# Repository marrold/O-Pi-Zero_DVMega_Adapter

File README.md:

# O-Pi-Zero_DVMega_Adapter

An adapter to allow the DVMega Digital Voice Modem to mount on an Orange Pi Zero.

### Notice

This is the second attempt at the PCB, and is so far untested. I can't make any guarantees it will work until they are manufactured and tested.

***PLEASE DON'T GET THIS BOARD MANUFACTURED UNTIL IT'S TESTED!!!***

### Pictures

### Licence

This project is licensed under the [Creative Commons CC BY-NC-SA 4.0](https://creativecommons.org/licenses/by-nc-sa/4.0/) licence.

You are free to share and adapt the code as required, however you *must* give appropriate credit and indicate what changes have been made. You must also distribute your adaptation under the same license. Commercial use is prohibited.

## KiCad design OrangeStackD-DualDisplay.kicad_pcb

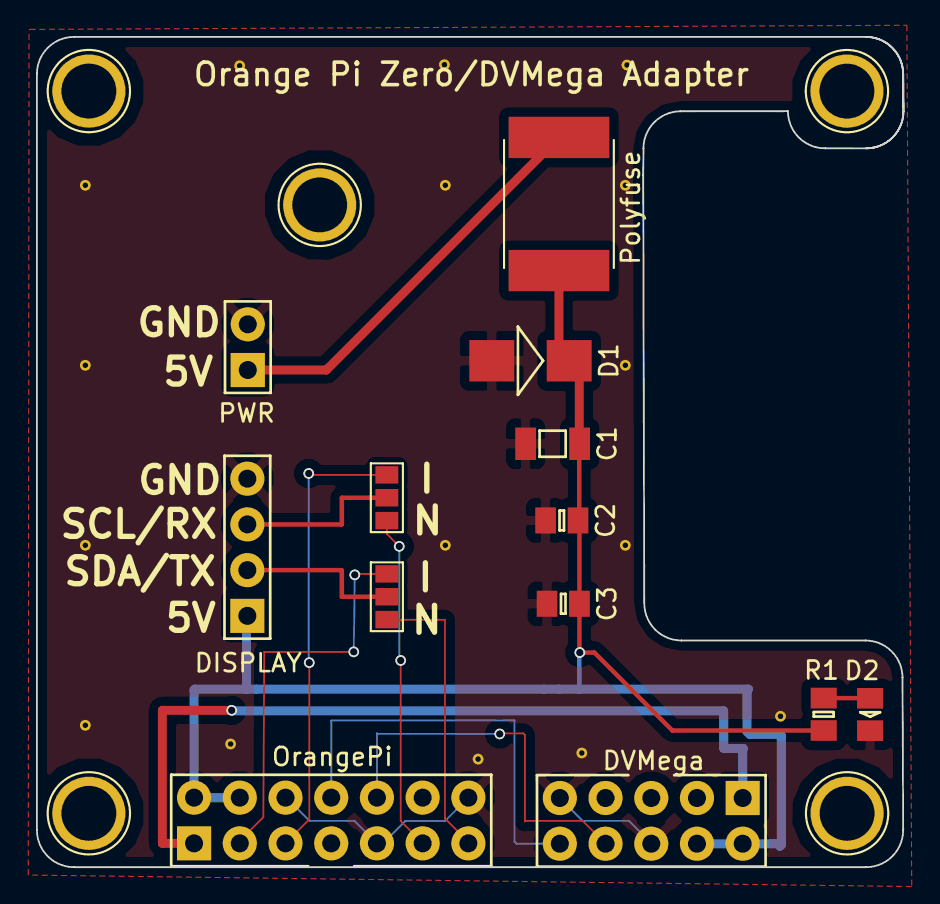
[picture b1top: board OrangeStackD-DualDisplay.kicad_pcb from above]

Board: 2 copper layers, 48.1 x 46.1 mm, 13 parts (0 on the bottom side), 13 nets.

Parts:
C1: 220uF; 1206
C2: 100nF; 0805
C3: 1nF; 0805
D1: ESD_DIODE; DO-214AA-SMB
D2: LED; 0805-LED
F1: Polyfuse; Fuse_SMD2920
J1: DISPLAY; SIL-254P-04
J2: OrangePi; DIL-254P-14
J3: DVMega; DIL-254P-10
J4, J5: GS3
J6: PWR; SIL-254P-02
R1: 680; 0805

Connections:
3v3: J2.1, J3.1
5v: C1.1, C2.1, C3.1, D1.1, F1.1, J1.1, J2.2, J2.4, J3.2, J3.4, R1.1
/SCL: J2.5, J5.1
/SCL/RX: J1.3, J5.2
/SDA: J2.3, J4.1
/SDA/TX: J1.2, J4.2
/UART1_RX: J2.10, J3.8
/UART1_TX: J2.8, J3.10
/UART2_RX: J2.11, J5.3
/UART2_TX: J2.13, J4.3
GND: C1.2, C2.2, C3.2, D1.2, D2.1, J1.4, J2.6, J2.9, J2.14, J3.6, J3.9, J6.2
unnamed: D2.2, R1.2
unnamed: F1.2, J6.1

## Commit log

2017-07-31 First Revision
2017-07-31 Adds pictures of PCB
2017-07-31 Updates README to include images
2017-07-31 Removes .DS_Store file
2017-07-31 Updates .gitignore
2017-07-31 Adds zipped gerbers
2017-07-31 Hopefully removes some more DS_Store files
2017-09-04 Update README.md
    Adds notification that this board doesnt work
2017-10-03 Fixes issue with DVMega connector, adds power filtering and safety features
2017-10-03 Moves capacitors into correct order
2017-10-03 Adds power LED
2017-10-03 Updates images
2017-10-03 Changes to sensible filenames
2017-10-03 Adds correct image
2017-10-03 Removes odd image
2017-10-03 Fixes rear image
2017-10-04 Adds license to README
